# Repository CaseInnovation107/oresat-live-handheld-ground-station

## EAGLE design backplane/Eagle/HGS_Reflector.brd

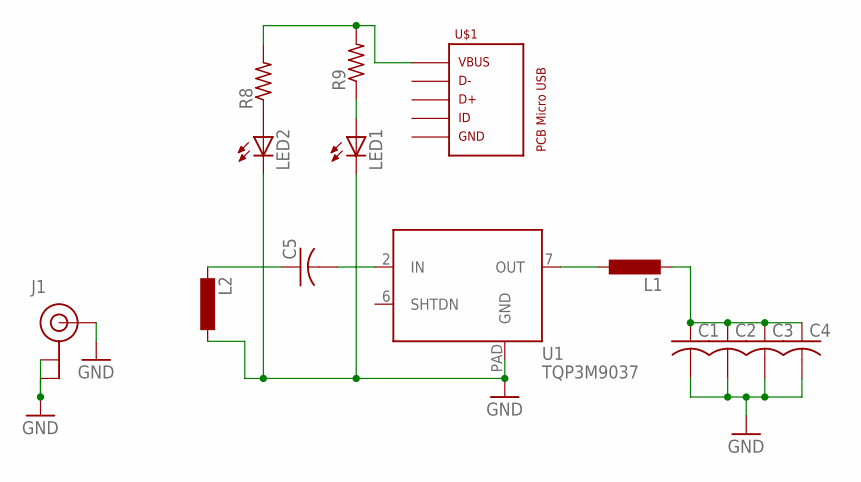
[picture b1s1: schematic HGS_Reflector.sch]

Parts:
C1, C2, C3, C4, C5: C-USC1210; C1210
J1: U.FL
L1, L2: L-EUL3216C; L3216C
LED1, LED2: LED_E; LED_1206
R8, R9: R-US_R0402; R0402
U1: TQP3M9037; DFN8-2X2-WITH-PAD
U$1: PCB_MICRO_USB_BSS_1; USB_TYPE_B_SS_1

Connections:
GND: C1.2, C2.2, C3.2, C4.2, J1.1 (GND), J1.2 (GND), J1.FEED (SIGNAL), L2.1, LED1.C, LED2.C, U1.PAD (GND)
unnamed: L1.1, U1.7 (OUT)
unnamed: C1.1, C2.1, C3.1, C4.1, L1.2
unnamed: C5.1, L2.2
unnamed: C5.2, U1.2 (IN)
unnamed: LED2.A, R8.1
unnamed: LED1.A, R9.1
unnamed: R8.2, R9.2, U$1.1

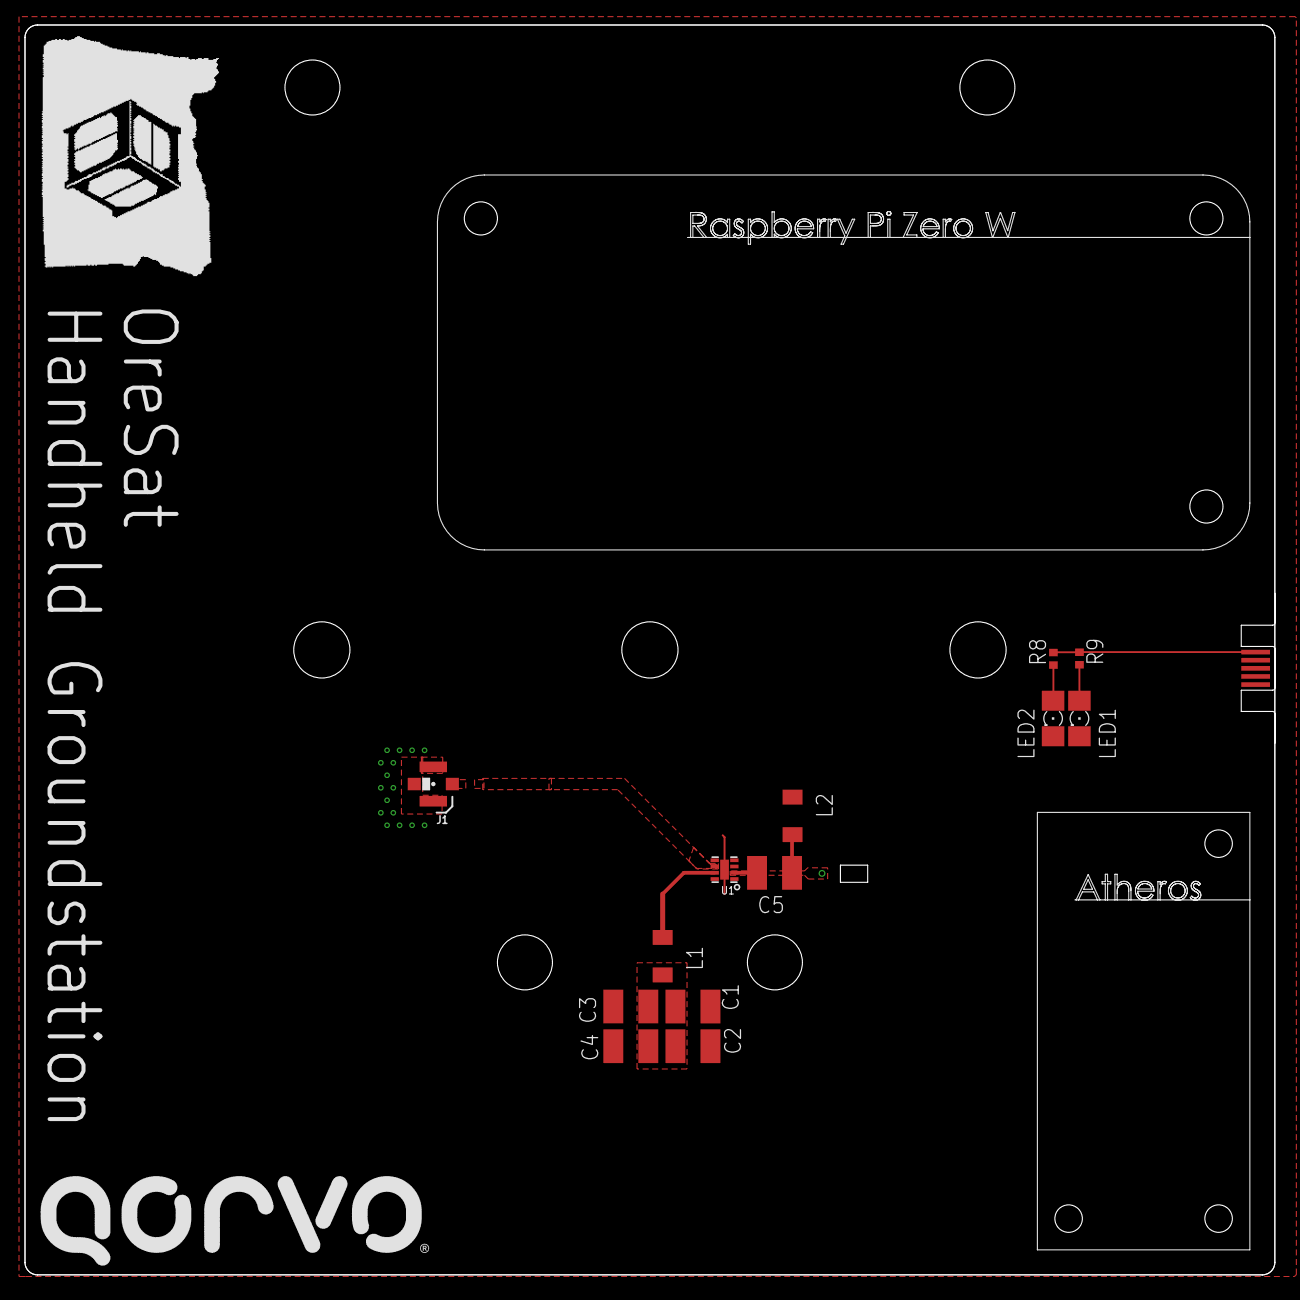
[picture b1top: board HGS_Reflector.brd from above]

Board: 4 copper layers, 100.0 x 100.0 mm, 14 parts (0 on the bottom side), 8 nets.

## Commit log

2020-07-19 This contains the updated version of HGS schematic on 7/19/20.
2020-07-19 I just deleted the unnessary folder containing an older version of the backplane.
2020-07-19 One more step to deleting those folders
2020-07-19 Renaming some files for consistency's sake.
2020-07-19 Just remembered to check through some layers on the schematic
2020-07-19 My EAGLE accidentally named something wrong, so I am fixing that.

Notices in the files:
parts and their libraries:
SparkFun-Connectors: Licensing: Creative Commons ShareAlike 4.0 International - https://creativecommons.org/licenses/by-sa/4.0
